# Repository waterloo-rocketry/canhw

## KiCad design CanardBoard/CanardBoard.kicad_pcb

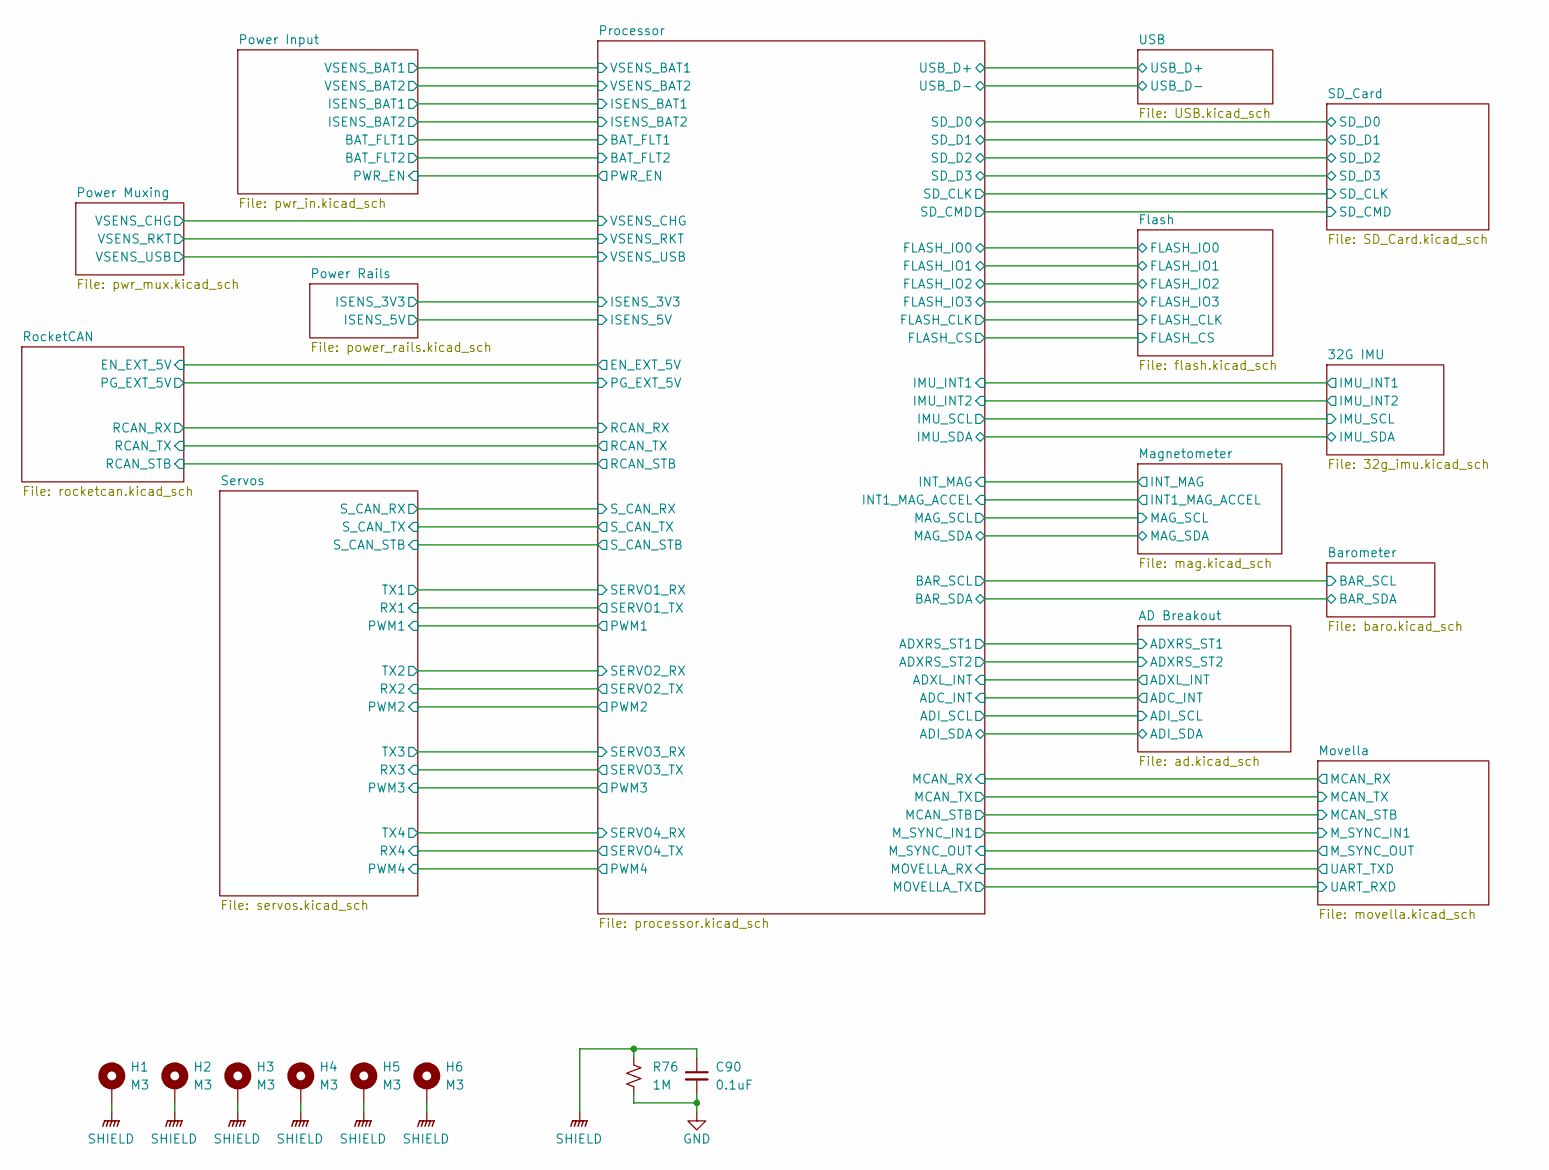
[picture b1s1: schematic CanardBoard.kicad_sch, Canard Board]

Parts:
C90: 0.1uF; C_0805_2012Metric
H1, H2, H3, H4, H5, H6: M3; MountingHole_3.2mm_M3_Pad
R76: 1M; R_0805_2012Metric

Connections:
GND: C90.2, R76.2; also elsewhere on the board
SHIELD: C90.1, H1.1, H2.1, H3.1, H4.1, H5.1, H6.1, R76.1

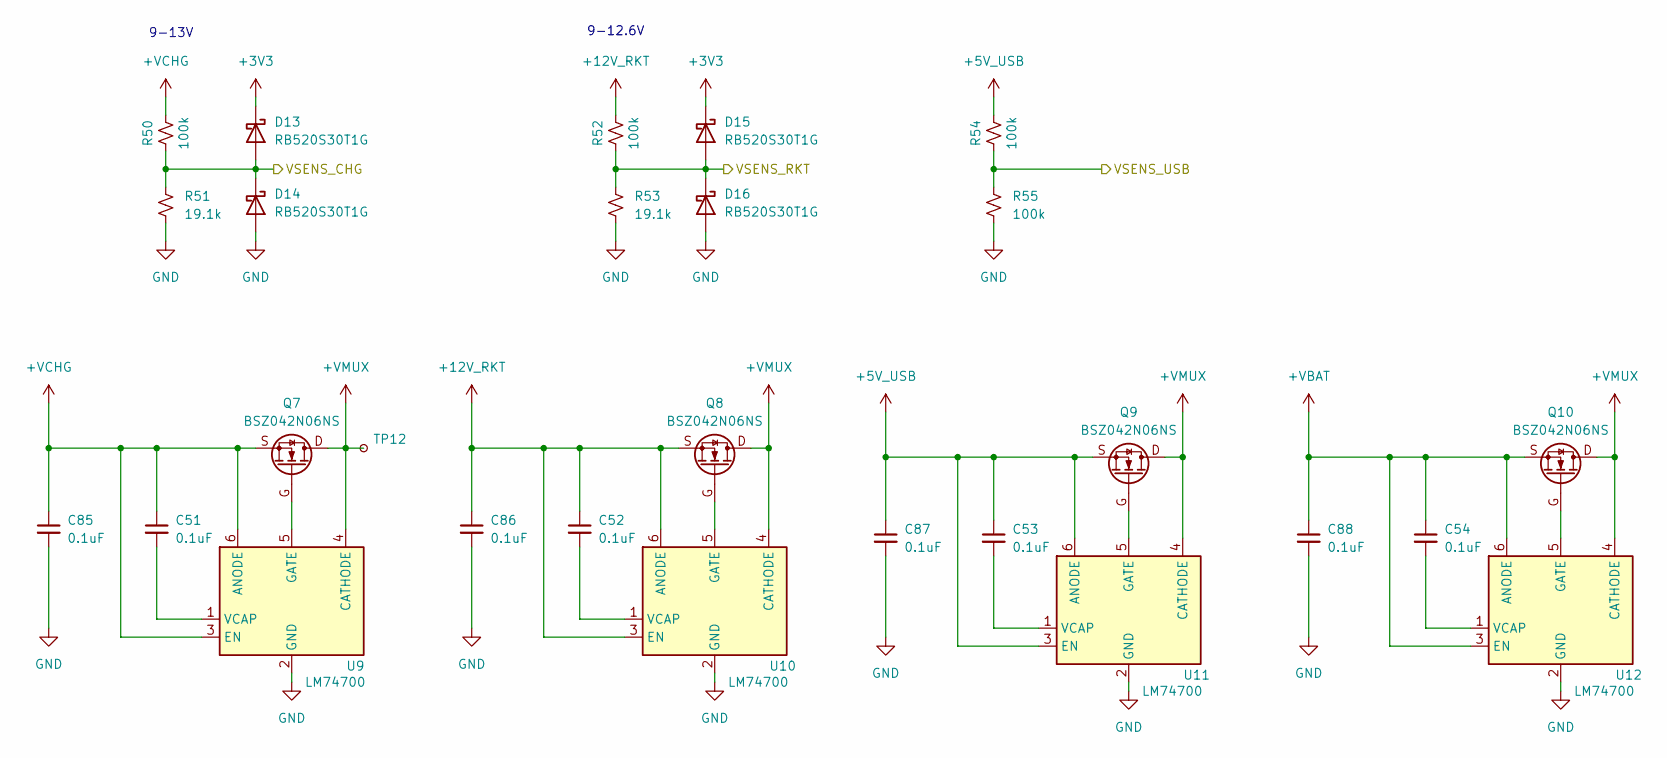
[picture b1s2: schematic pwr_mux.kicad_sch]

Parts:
C51, C52, C53, C54, C85, C86, C87, C88: 0.1uF; C_0603_1608Metric; LCSC Part # C49678
D13, D14, D15, D16: RB520S30T1G; D_SOD-523
Q7, Q8, Q9, Q10: BSZ042N06NS; Infineon-PG-TSDSON-8
R50, R52, R54: 100k; R_0402_1005Metric; LCSC Part # C17630
R51, R53: 19.1k; R_0402_1005Metric
R55: 100k; R_0402_1005Metric
TP12: VMUX; TestPoint_Pad_D1.0mm
U9, U10, U11, U12: LM74700; SOT-23-6

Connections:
+3V3: D13.1 (K), D15.1 (K); also elsewhere on the board
+5V_USB: C53.1, C87.1, Q9.S, R54.1, U11.3 (EN), U11.6 (ANODE); also elsewhere on the board
+12V_RKT: C52.1, C86.1, Q8.S, R52.1, U10.3 (EN), U10.6 (ANODE); also elsewhere on the board
+VBAT: C54.1, C88.1, Q10.S, U12.3 (EN), U12.6 (ANODE); also elsewhere on the board
+VCHG: C51.1, C85.1, Q7.S, R50.1, U9.3 (EN), U9.6 (ANODE); also elsewhere on the board
+VMUX: Q7.D, Q8.D, Q9.D, Q10.D, TP12.1, U9.4 (CATHODE), U10.4 (CATHODE), U11.4 (CATHODE), U12.4 (CATHODE); also elsewhere on the board
/Power Muxing/VSENS_CHG: D13.2 (A), D14.1 (K), R50.2, R51.2; also elsewhere on the board
/Power Muxing/VSENS_RKT: D15.2 (A), D16.1 (K), R52.2, R53.2; also elsewhere on the board
/Power Muxing/VSENS_USB: R54.2, R55.2; also elsewhere on the board
GND: C85.2, C86.2, C87.2, C88.2, D14.2 (A), D16.2 (A), R51.1, R53.1, R55.1, U9.2 (GND), U10.2 (GND), U11.2 (GND), U12.2 (GND); also elsewhere on the board
unnamed: Q7.G, U9.5 (GATE)
unnamed: C51.2, U9.1 (VCAP)
unnamed: Q8.G, U10.5 (GATE)
unnamed: C52.2, U10.1 (VCAP)
unnamed: Q9.G, U11.5 (GATE)
unnamed: C53.2, U11.1 (VCAP)
unnamed: Q10.G, U12.5 (GATE)
unnamed: C54.2, U12.1 (VCAP)

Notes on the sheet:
9-13V
9-12.6V

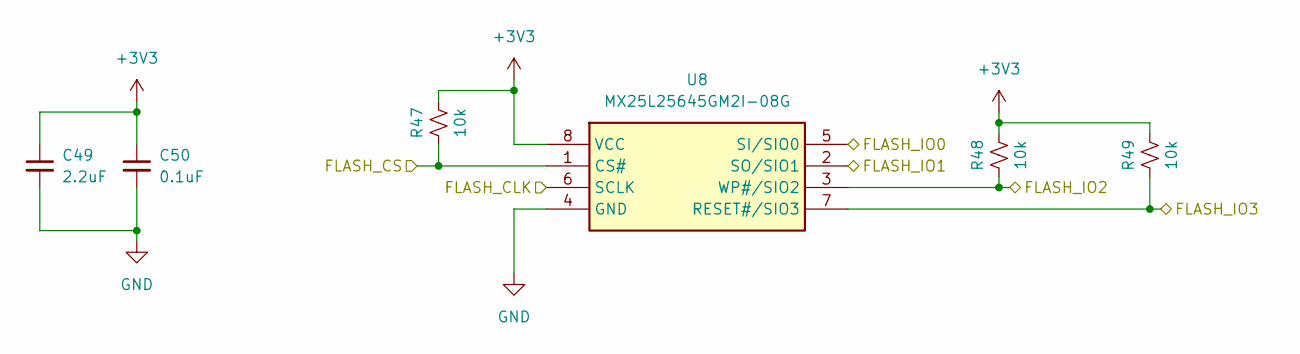
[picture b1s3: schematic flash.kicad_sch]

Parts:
C49: 2.2uF; C_0402_1005Metric; LCSC Part # C49678
C50: 0.1uF; C_0402_1005Metric; LCSC Part # C49678
R47, R48, R49: 10k; R_0402_1005Metric; LCSC Part # C17414
U8: MX25L25645GM2I-08G; Mouser Part Number 95-25L25645GM2I0TR

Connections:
+3V3: C49.1, C50.1, R47.1, R48.1, R49.1, U8.8 (VCC); also elsewhere on the board
/Flash/FLASH_CLK: U8.6 (SCLK); also elsewhere on the board
/Flash/FLASH_CS: R47.2, U8.1 (CS#); also elsewhere on the board
/Flash/FLASH_IO0: U8.5 (SI/SIO0); also elsewhere on the board
/Flash/FLASH_IO1: U8.2 (SO/SIO1); also elsewhere on the board
/Flash/FLASH_IO2: R48.2, U8.3 (WP#/SIO2); also elsewhere on the board
/Flash/FLASH_IO3: R49.2, U8.7 (RESET#/SIO3); also elsewhere on the board
GND: C49.2, C50.2, U8.4 (GND); also elsewhere on the board

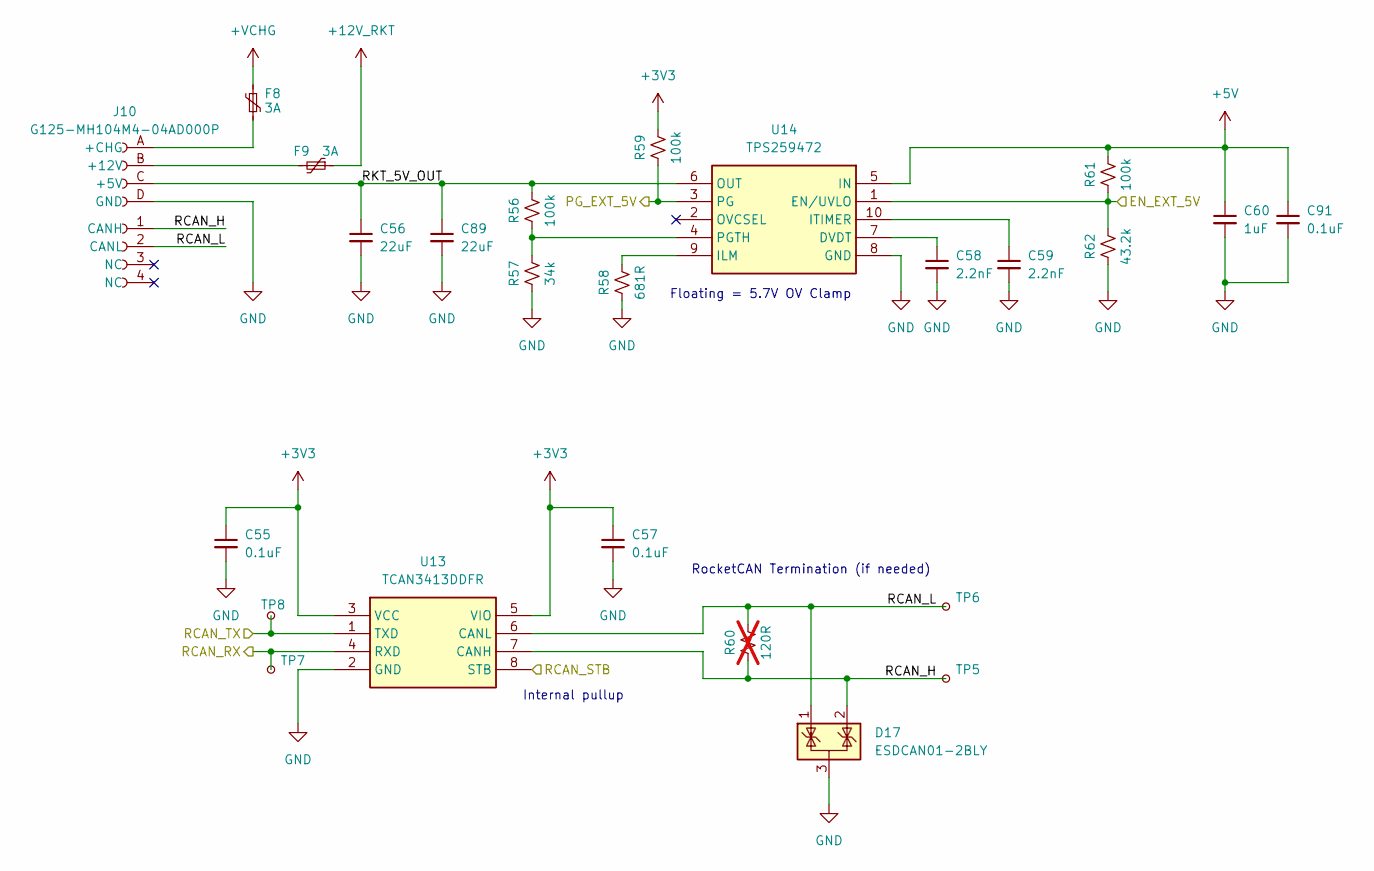
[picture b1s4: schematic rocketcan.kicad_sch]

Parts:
C55, C57, C91: 0.1uF; C_0402_1005Metric; LCSC Part # C49678
C56, C89: 22uF; C_0805_2012Metric; LCSC Part # C49678
C58, C59: 2.2nF; C_0402_1005Metric; LCSC Part # C49678
C60: 1uF; C_0402_1005Metric; LCSC Part # C49678
D17: ESDCAN01-2BLY; SOT-23
F8, F9: 3A; Fuse_0805_2012Metric
J10: G125-MH104M4-04AD000P; connector_Harwin_G125-MH104M4-04AD000P
R56, R59, R61: 100k; R_0402_1005Metric; LCSC Part # C17630
R57: 34k; R_0402_1005Metric; LCSC Part # C17630
R58: 681R; R_0402_1005Metric; LCSC Part # C17630
R60: 120R; R_0805_2012Metric; LCSC Part # C17630; not fitted
R62: 43.2k; R_0402_1005Metric; LCSC Part # C17630
TP5: RCAN_H; TestPoint_Pad_D1.0mm
TP6: RCAN_L; TestPoint_Pad_D1.0mm
TP7: RCAN_RX; TestPoint_Pad_D1.0mm
TP8: RCAN_TX; TestPoint_Pad_D1.0mm
U13: TCAN3413DDFR; Mouser Part Number 595-TCAN3413DDFR
U14: TPS259472; TPS25947xx; Mouser Part Number 595-TPS25210LRPWR

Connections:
+3V3: C55.1, C57.1, R59.1, U13.3 (VCC), U13.5 (VIO); also elsewhere on the board
+5V: C60.1, C91.1, R61.1, U14.5 (IN); also elsewhere on the board
+12V_RKT: F9.1; also elsewhere on the board
+VCHG: F8.1; also elsewhere on the board
/Processor/EN_EXT_5V: R61.2, R62.1, U14.1 (EN/UVLO); also elsewhere on the board
/Processor/PG_EXT_5V: R59.2, U14.3 (PG); also elsewhere on the board
/Processor/RCAN_RX: TP7.1, U13.4 (RXD); also elsewhere on the board
/Processor/RCAN_STB: U13.8 (STB); also elsewhere on the board
/Processor/RCAN_TX: TP8.1, U13.1 (TXD); also elsewhere on the board
/RocketCAN/RCAN_H: D17.2 (K), J10.1 (CANH), R60.2, TP5.1, U13.7 (CANH)
/RocketCAN/RCAN_L: D17.1 (K), J10.2 (CANL), R60.1, TP6.1, U13.6 (CANL)
/RocketCAN/RKT_5V_OUT: C56.1, C89.1, J10.C (+5V), R56.1, U14.6 (OUT)
GND: C55.2, C56.2, C57.2, C58.2, C59.2, C60.2, C89.2, C91.2, D17.3 (A), J10.D (GND), R57.2, R58.2, R62.2, U13.2 (GND), U14.8 (GND); also elsewhere on the board
unnamed: F9.2, J10.B (+12V)
unnamed: F8.2, J10.A (+CHG)
unnamed: C58.1, U14.7 (DVDT)
unnamed: R58.1, U14.9 (ILM)
unnamed: C59.1, U14.10 (ITIMER)
unnamed: R56.2, R57.1, U14.4 (PGTH)

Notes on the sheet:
Floating = 5.7V OV Clamp
RocketCAN Termination (if needed)
Internal pullup

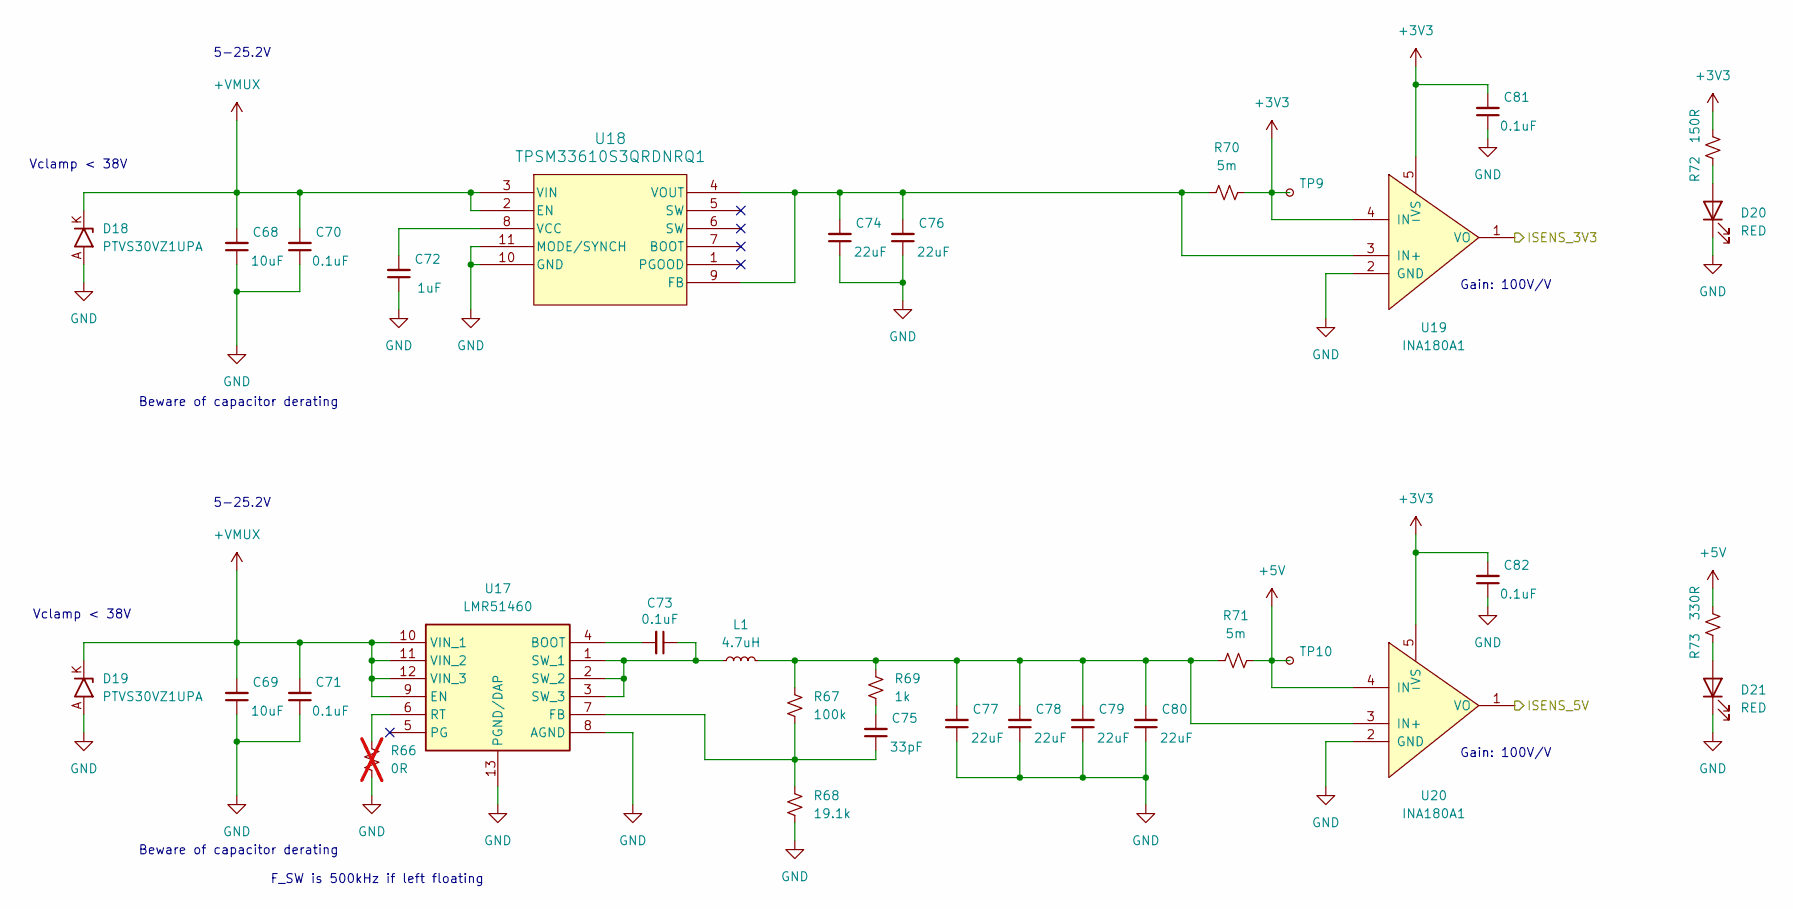
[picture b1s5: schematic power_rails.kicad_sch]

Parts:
C68, C69: 10uF; C_1210_3225Metric; LCSC Part # C49678
C70, C71: 0.1uF; C_0603_1608Metric; LCSC Part # C49678
C72: 1uF; C_0402_1005Metric; LCSC Part # C49678
C73, C81, C82: 0.1uF; C_0402_1005Metric; LCSC Part # C49678
C74, C76, C77, C78, C79, C80: 22uF; C_0805_2012Metric; LCSC Part # C49678
C75: 33pF; C_0402_1005Metric; LCSC Part # C49678
D18, D19: PTVS30VZ1UPA; PTVS30VZ1UPAZ
D20, D21: RED; LED_0603_1608Metric
L1: 4.7uH; SRP7050WA; MPN SRP7050WA-4R7M
R66: 0R; R_0402_1005Metric; not fitted
R67: 100k; R_0402_1005Metric
R68: 19.1k; R_0402_1005Metric
R69: 1k; R_0402_1005Metric
R70, R71: 5m; R_0805_2012Metric
R72: 150R; R_0402_1005Metric; LCSC Part # C17471
R73: 330R; R_0402_1005Metric; LCSC Part # C17471
TP9: 3V3; TestPoint_Pad_D1.0mm
TP10: 5V; TestPoint_Pad_D1.0mm
U17: LMR51460
U18: TPSM33610S3QRDNRQ1; TPSM33606S3QRDNRQ1
U19, U20: INA180A1; SOT-23-5

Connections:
+3V3: C81.2, C82.2, R70.1, R72.1, TP9.1, U19.4 (IN-), U19.5 (VS), U20.5 (VS); also elsewhere on the board
+5V: R71.1, R73.1, TP10.1, U20.4 (IN-); also elsewhere on the board
+VMUX: C68.2, C69.2, C70.2, C71.2, D18.K, D19.K, U17.9 (EN), U17.10 (VIN_1), U17.11 (VIN_2), U17.12 (VIN_3), U18.2 (EN), U18.3 (VIN); also elsewhere on the board
/Power Rails/ISENS_3V3: U19.1 (VO); also elsewhere on the board
/Power Rails/ISENS_5V: U20.1 (VO); also elsewhere on the board
GND: C68.1, C69.1, C70.1, C71.1, C72.1, C74.1, C76.1, C77.1, C78.1, C79.1, C80.1, C81.1, C82.1, D18.A, D19.A, D20.1 (K), D21.1 (K), R66.1, R68.1, U17.8 (AGND), U17.13 (PGND/DAP), U18.10 (GND), U18.11 (MODE/SYNCH), U19.2 (GND), U20.2 (GND); also elsewhere on the board
unnamed: C75.2, R69.1
unnamed: D20.2 (A), R72.2
unnamed: D21.2 (A), R73.2
unnamed: C73.2, U17.4 (BOOT)
unnamed: C75.1, R67.1, R68.2, U17.7 (FB)
unnamed: R66.2, U17.6 (RT)
unnamed: C73.1, L1.1, U17.1 (SW_1), U17.2 (SW_2), U17.3 (SW_3)
unnamed: C74.2, C76.2, R70.2, U18.4 (VOUT), U18.9 (FB), U19.3 (IN+)
unnamed: C72.2, U18.8 (VCC)
unnamed: C77.2, C78.2, C79.2, C80.2, L1.2, R67.2, R69.2, R71.2, U20.3 (IN+)

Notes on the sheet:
5-25.2V
Beware of capacitor derating
F_SW is 500kHz if left floating
Gain: 100V/V
Vclamp < 38V

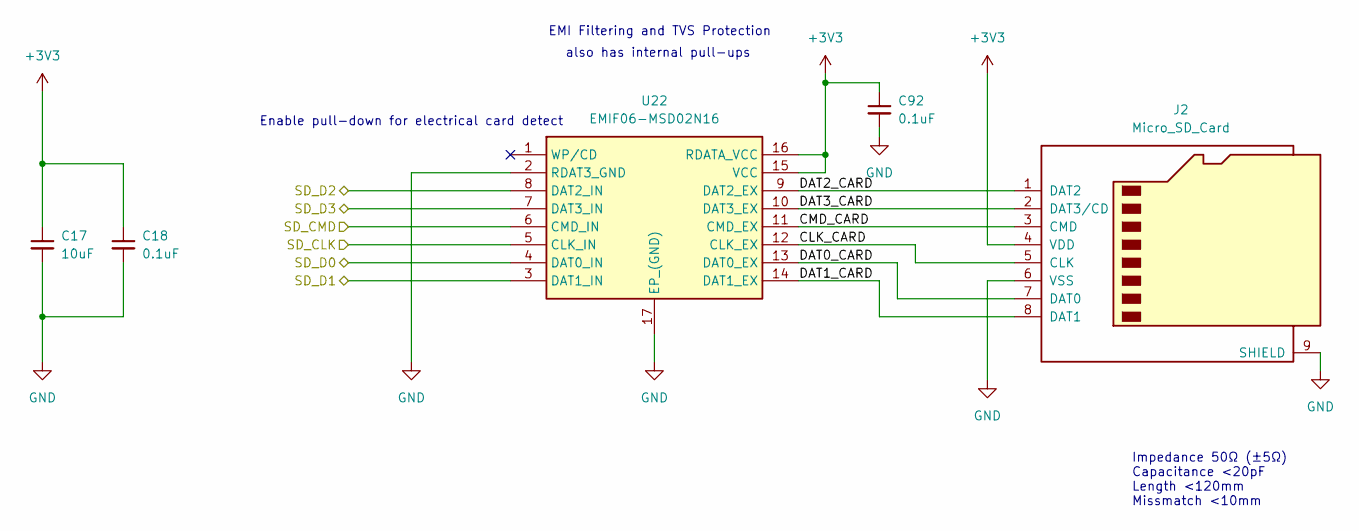
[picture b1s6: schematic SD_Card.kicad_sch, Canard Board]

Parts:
C17: 10uF; C_0603_1608Metric; LCSC Part # C49678
C18, C92: 0.1uF; C_0402_1005Metric; LCSC Part # C49678
J2: Micro_SD_Card; microSD_HC_Molex_47219-2001
U22: EMIF06-MSD02N16; EMIF06MSD02N16

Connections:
+3V3: C17.1, C18.1, C92.1, J2.4 (VDD), U22.15 (VCC), U22.16 (RDATA_VCC); also elsewhere on the board
/Processor/SD_CLK: U22.5 (CLK_IN); also elsewhere on the board
/Processor/SD_CMD: U22.6 (CMD_IN); also elsewhere on the board
/Processor/SD_D0: U22.4 (DAT0_IN); also elsewhere on the board
/Processor/SD_D1: U22.3 (DAT1_IN); also elsewhere on the board
/Processor/SD_D2: U22.8 (DAT2_IN); also elsewhere on the board
/Processor/SD_D3: U22.7 (DAT3_IN); also elsewhere on the board
/SD_Card/CLK_CARD: J2.5 (CLK), U22.12 (CLK_EX)
/SD_Card/CMD_CARD: J2.3 (CMD), U22.11 (CMD_EX)
/SD_Card/DAT0_CARD: J2.7 (DAT0), U22.13 (DAT0_EX)
/SD_Card/DAT1_CARD: J2.8 (DAT1), U22.14 (DAT1_EX)
/SD_Card/DAT2_CARD: J2.1 (DAT2), U22.9 (DAT2_EX)
/SD_Card/DAT3_CARD: J2.2 (DAT3/CD), U22.10 (DAT3_EX)
GND: C17.2, C18.2, C92.2, J2.6 (VSS), J2.9 (SHIELD), U22.2 (RDAT3_GND), U22.17 (EP_(GND)); also elsewhere on the board

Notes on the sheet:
also has internal pull-ups
Impedance 50Ω (±5Ω) Capacitance <20pF Length <120mm Missmatch <10mm
EMI Filtering and TVS Protection
Enable pull-down for electrical card detect

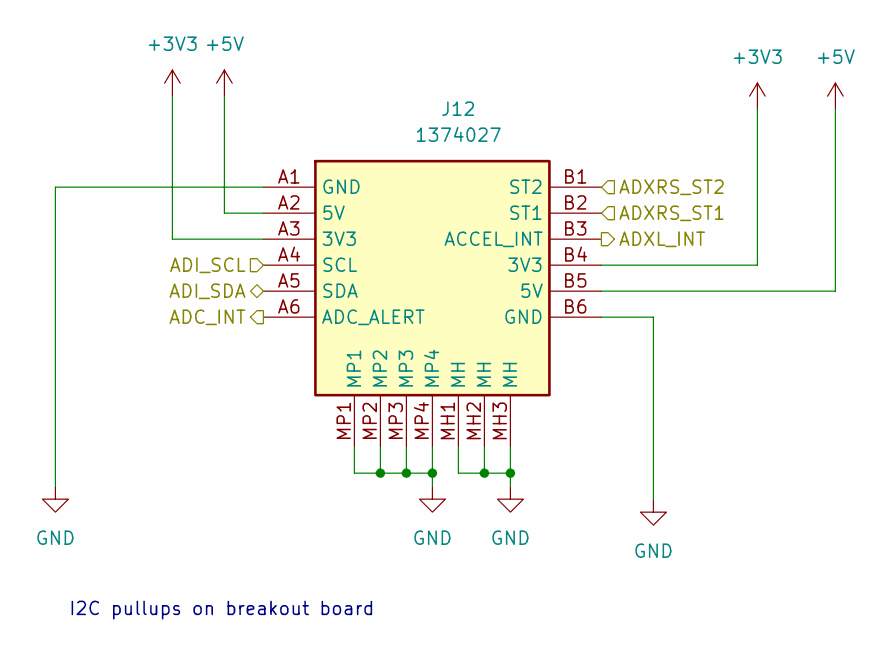
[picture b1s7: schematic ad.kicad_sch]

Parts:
J12: 1374027; Mouser Part Number 651-1374027

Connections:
+3V3: J12.A3 (3V3), J12.B4 (3V3); also elsewhere on the board
+5V: J12.A2 (5V), J12.B5 (5V); also elsewhere on the board
/AD Breakout/ADC_INT: J12.A6 (ADC_ALERT); also elsewhere on the board
/AD Breakout/ADI_SCL: J12.A4 (SCL); also elsewhere on the board
/AD Breakout/ADI_SDA: J12.A5 (SDA); also elsewhere on the board
/AD Breakout/ADXL_INT: J12.B3 (ACCEL_INT); also elsewhere on the board
/AD Breakout/ADXRS_ST1: J12.B2 (ST1); also elsewhere on the board
/AD Breakout/ADXRS_ST2: J12.B1 (ST2); also elsewhere on the board
GND: J12.A1 (GND), J12.B6 (GND), J12.MH1 (MH), J12.MH2 (MH), J12.MH3 (MH), J12.MP1, J12.MP2, J12.MP3, J12.MP4; also elsewhere on the board

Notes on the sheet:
I2C pullups on breakout board

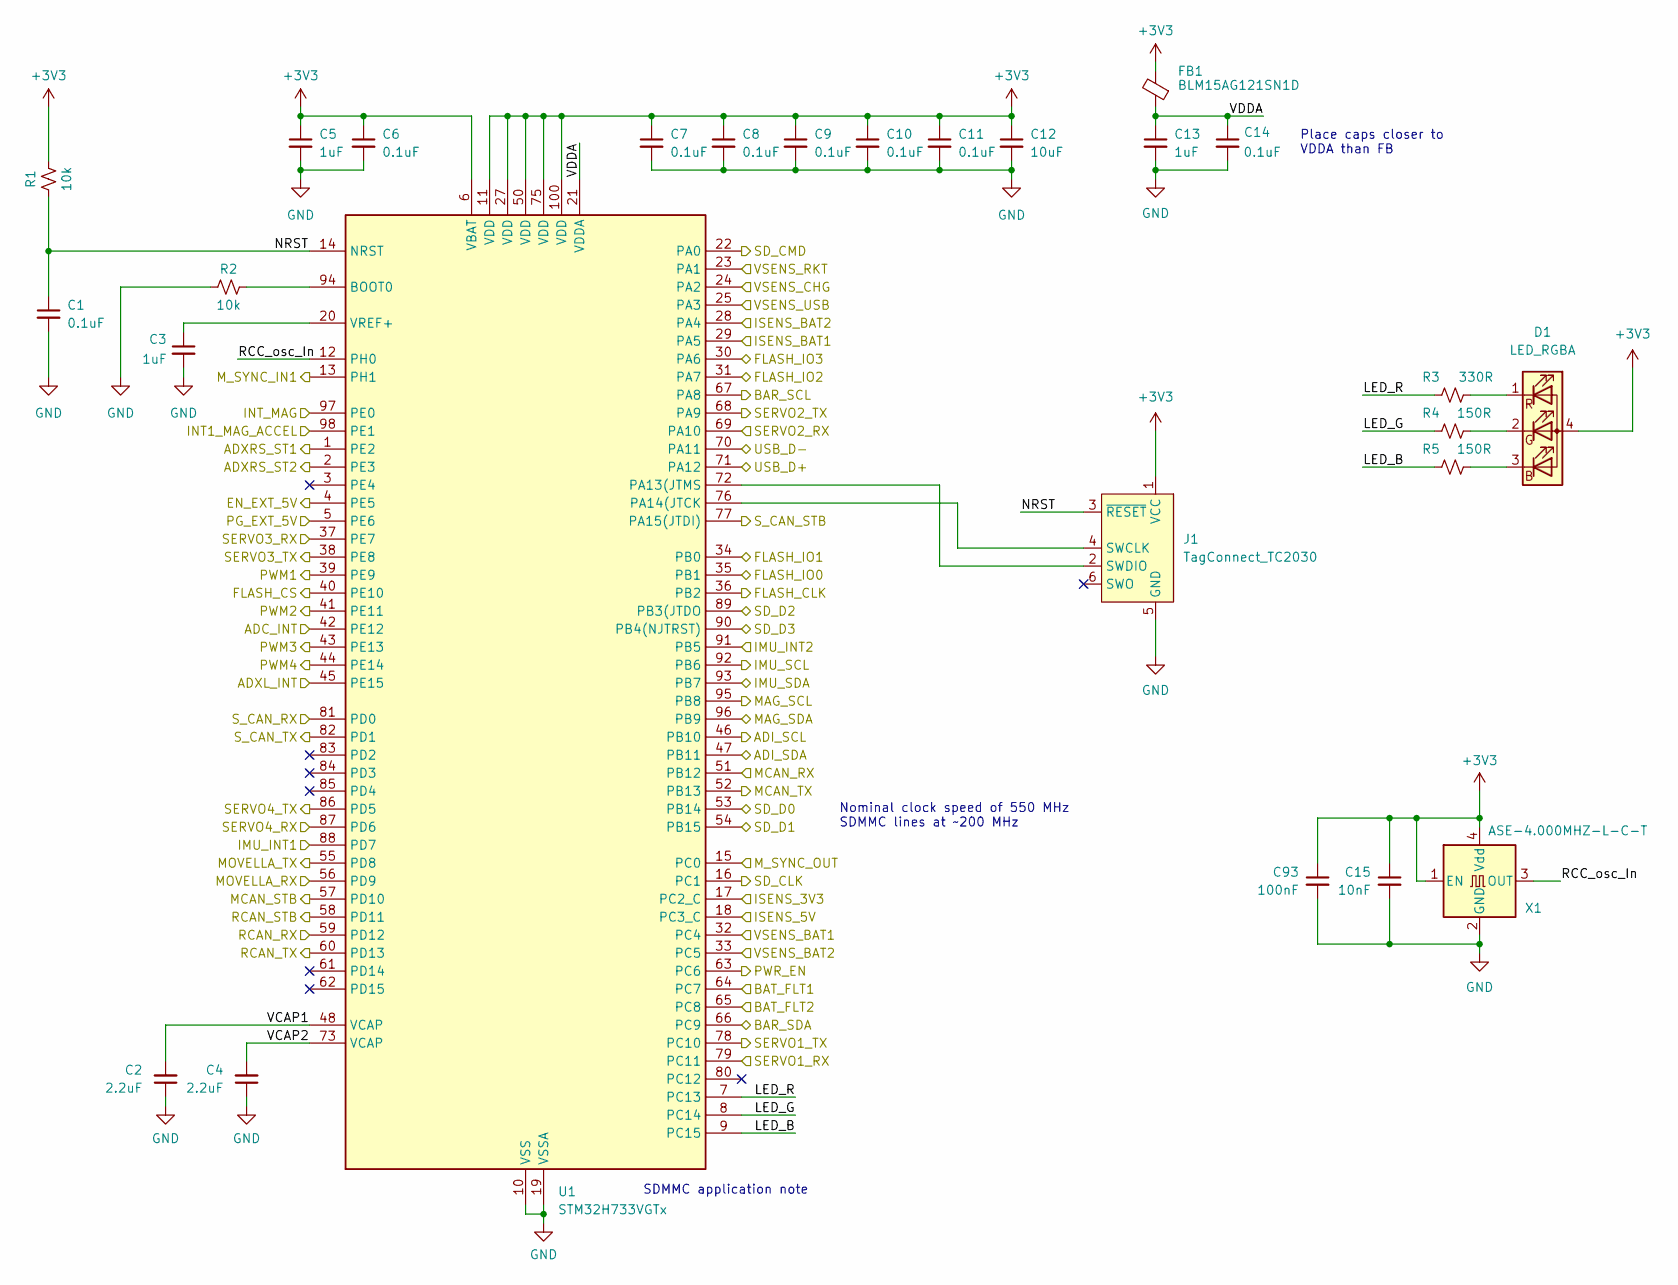
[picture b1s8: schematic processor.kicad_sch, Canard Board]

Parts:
C1, C6, C7, C8, C9, C10, C11, C14: 0.1uF; C_0402_1005Metric; LCSC Part # C49678
C2, C4: 2.2uF; C_0402_1005Metric; LCSC Part # C377773
C3, C5, C13: 1uF; C_0402_1005Metric; LCSC Part # C28323
C12: 10uF; C_0603_1608Metric; LCSC Part # C49678
C15: 10nF; C_0402_1005Metric; LCSC Part # C1710
C93: 100nF; C_0402_1005Metric; LCSC Part # C1710
D1: LED_RGBA; EAST1616RGBB2
FB1: BLM15AG121SN1D; C_0402_1005Metric
J1: TagConnect_TC2030; Tag-Connect_TC2030-IDC-FP_2x03_P1.27mm_Vertical
R1, R2: 10k; R_0402_1005Metric; LCSC Part # C17414
R3: 330R; R_0402_1005Metric; LCSC Part # C17630
R4, R5: 150R; R_0402_1005Metric; LCSC Part # C17471
U1: STM32H733VGTx; LQFP-100_14x14mm_P0.5mm; LCSC Part # C730160
X1: ASE-4.000MHZ-L-C-T; Oscillator_SMD_Abracon_ASE-4Pin_3.2x2.5mm; LCSC Part # C437121

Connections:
+3V3: C5.1, C6.1, C7.1, C8.1, C9.1, C10.1, C11.1, C12.1, C15.1, C93.1, D1.4 (A), FB1.2, J1.1 (VCC), R1.1, U1.6 (VBAT), U1.11 (VDD), U1.27 (VDD), U1.50 (VDD), U1.75 (VDD), U1.100 (VDD), X1.1 (EN), X1.4 (Vdd); also elsewhere on the board
/32G IMU/IMU_INT1: U1.88 (PD7); also elsewhere on the board
/32G IMU/IMU_INT2: U1.91 (PB5); also elsewhere on the board
/32G IMU/IMU_SCL: U1.92 (PB6); also elsewhere on the board
/32G IMU/IMU_SDA: U1.93 (PB7); also elsewhere on the board
/AD Breakout/ADC_INT: U1.42 (PE12); also elsewhere on the board
/AD Breakout/ADI_SCL: U1.46 (PB10); also elsewhere on the board
/AD Breakout/ADI_SDA: U1.47 (PB11); also elsewhere on the board
/AD Breakout/ADXL_INT: U1.45 (PE15); also elsewhere on the board
/AD Breakout/ADXRS_ST1: U1.1 (PE2); also elsewhere on the board
/AD Breakout/ADXRS_ST2: U1.2 (PE3); also elsewhere on the board
/Barometer/BAR_SCL: U1.67 (PA8); also elsewhere on the board
/Barometer/BAR_SDA: U1.66 (PC9); also elsewhere on the board
/Flash/FLASH_CLK: U1.36 (PB2); also elsewhere on the board
/Flash/FLASH_CS: U1.40 (PE10); also elsewhere on the board
/Flash/FLASH_IO0: U1.35 (PB1); also elsewhere on the board
/Flash/FLASH_IO1: U1.34 (PB0); also elsewhere on the board
/Flash/FLASH_IO2: U1.31 (PA7); also elsewhere on the board
/Flash/FLASH_IO3: U1.30 (PA6); also elsewhere on the board
/Magnetometer/INT1_MAG_ACCEL: U1.98 (PE1); also elsewhere on the board
/Magnetometer/INT_MAG: U1.97 (PE0); also elsewhere on the board
/Magnetometer/MAG_SCL: U1.95 (PB8); also elsewhere on the board
/Magnetometer/MAG_SDA: U1.96 (PB9); also elsewhere on the board
/Movella/MCAN_RX: U1.51 (PB12); also elsewhere on the board
/Movella/MCAN_STB: U1.57 (PD10); also elsewhere on the board
/Movella/MCAN_TX: U1.52 (PB13); also elsewhere on the board
/Movella/M_SYNC_IN1: U1.13 (PH1); also elsewhere on the board
/Movella/M_SYNC_OUT: U1.15 (PC0); also elsewhere on the board
/Movella/UART_RXD: U1.55 (PD8); also elsewhere on the board
/Movella/UART_TXD: U1.56 (PD9); also elsewhere on the board
/Power Input/BAT_FLT1: U1.64 (PC7); also elsewhere on the board
/Power Input/BAT_FLT2: U1.65 (PC8); also elsewhere on the board
/Power Input/ISENS_BAT1: U1.29 (PA5); also elsewhere on the board
/Power Input/ISENS_BAT2: U1.28 (PA4); also elsewhere on the board
/Power Input/PWR_EN: U1.63 (PC6); also elsewhere on the board
/Power Input/VSENS_BAT1: U1.32 (PC4); also elsewhere on the board
/Power Input/VSENS_BAT2: U1.33 (PC5); also elsewhere on the board
/Power Muxing/VSENS_CHG: U1.24 (PA2); also elsewhere on the board
/Power Muxing/VSENS_RKT: U1.23 (PA1); also elsewhere on the board
/Power Muxing/VSENS_USB: U1.25 (PA3); also elsewhere on the board
/Power Rails/ISENS_3V3: U1.17 (PC2_C); also elsewhere on the board
/Power Rails/ISENS_5V: U1.18 (PC3_C); also elsewhere on the board
/Processor/EN_EXT_5V: U1.4 (PE5); also elsewhere on the board
/Processor/LED_B: R5.2, U1.9 (PC15)
/Processor/LED_G: R4.2, U1.8 (PC14)
/Processor/LED_R: R3.2, U1.7 (PC13)
/Processor/NRST: C1.1, J1.3 (~RESET), R1.2, U1.14 (NRST)
/Processor/PG_EXT_5V: U1.5 (PE6); also elsewhere on the board
/Processor/PWM1: U1.39 (PE9); also elsewhere on the board
/Processor/PWM2: U1.41 (PE11); also elsewhere on the board
/Processor/PWM3: U1.43 (PE13); also elsewhere on the board
/Processor/PWM4: U1.44 (PE14); also elsewhere on the board
/Processor/RCAN_RX: U1.59 (PD12); also elsewhere on the board
/Processor/RCAN_STB: U1.58 (PD11); also elsewhere on the board
/Processor/RCAN_TX: U1.60 (PD13); also elsewhere on the board
/Processor/RCC_osc_In: U1.12 (PH0), X1.3 (OUT)
/Processor/SD_CLK: U1.16 (PC1); also elsewhere on the board
/Processor/SD_CMD: U1.22 (PA0); also elsewhere on the board
/Processor/SD_D0: U1.53 (PB14); also elsewhere on the board
/Processor/SD_D1: U1.54 (PB15); also elsewhere on the board
/Processor/SD_D2: U1.89 (PB3(JTDO); also elsewhere on the board
/Processor/SD_D3: U1.90 (PB4(NJTRST)); also elsewhere on the board
/Processor/SERVO1_RX: U1.79 (PC11); also elsewhere on the board
/Processor/SERVO1_TX: U1.78 (PC10); also elsewhere on the board
/Processor/SERVO2_RX: U1.69 (PA10); also elsewhere on the board
/Processor/SERVO2_TX: U1.68 (PA9); also elsewhere on the board
/Processor/SERVO3_RX: U1.37 (PE7); also elsewhere on the board
/Processor/SERVO3_TX: U1.38 (PE8); also elsewhere on the board
/Processor/SERVO4_RX: U1.87 (PD6); also elsewhere on the board
/Processor/SERVO4_TX: U1.86 (PD5); also elsewhere on the board
/Processor/S_CAN_RX: U1.81 (PD0); also elsewhere on the board
/Processor/S_CAN_STB: U1.77 (PA15(JTDI)); also elsewhere on the board
/Processor/S_CAN_TX: U1.82 (PD1); also elsewhere on the board
/Processor/USB_D+: U1.71 (PA12); also elsewhere on the board
/Processor/USB_D-: U1.70 (PA11); also elsewhere on the board
/Processor/VCAP1: C2.2, U1.48 (VCAP)
/Processor/VCAP2: C4.2, U1.73 (VCAP)
/Processor/VDDA: C13.1, C14.1, FB1.1, U1.21 (VDDA)
GND: C1.2, C2.1, C3.2, C4.1, C5.2, C6.2, C7.2, C8.2, C9.2, C10.2, C11.2, C12.2, C13.2, C14.2, C15.2, C93.2, J1.5 (GND), R2.2, U1.10 (VSS), U1.19 (VSSA), U1.26 (VSS), U1.49 (VSS), U1.74 (VSS), U1.99 (VSS), X1.2 (GND); also elsewhere on the board
unnamed: D1.3 (BK), R5.1
unnamed: D1.2 (GK), R4.1
unnamed: D1.1 (RK), R3.1
unnamed: J1.4 (SWCLK), U1.76 (PA14(JTCK)
unnamed: J1.2 (SWDIO), U1.72 (PA13(JTMS)
unnamed: R2.1, U1.94 (BOOT0)
unnamed: C3.1, U1.20 (VREF+)

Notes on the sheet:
SDMMC application note
Place caps closer to VDDA than FB
Nominal clock speed of 550 MHz SDMMC lines at ~200 MHz

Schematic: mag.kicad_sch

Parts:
C61, C62: 0.1uF; C_0402_1005Metric; LCSC Part # C49678
C63: 4.7uF; C_0402_1005Metric; LCSC Part # C49678
C64: 220nF; C_0402_1005Metric; LCSC Part # C49678
R63, R64: 1k; R_0402_1005Metric
U15: LSM303AGR; LGA-12_2x2mm_P0.5mm

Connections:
+3V3: C61.2, C62.2, C63.2, R63.2, R64.2, U15.2 (CS_XL), U15.3 (CS_MAG), U15.9 (VDD), U15.10 (VDDIO); also elsewhere on the board
/Magnetometer/INT1_MAG_ACCEL: U15.12 (INT_1_XL); also elsewhere on the board
/Magnetometer/INT_MAG: U15.7 (INT_MAG/DRDY); also elsewhere on the board
/Magnetometer/MAG_SCL: R64.1, U15.1 (SCL/SPC); also elsewhere on the board
/Magnetometer/MAG_SDA: R63.1, U15.4 (SDA/SDI/SDO); also elsewhere on the board
GND: C61.1, C62.1, C63.1, C64.1, U15.6 (GND), U15.8 (GND); also elsewhere on the board
unnamed: C64.2, U15.5 (C1)

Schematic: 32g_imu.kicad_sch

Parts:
C83, C84: 0.1uF; C_0402_1005Metric; LCSC Part # C49678
R74, R75: 1k; R_0402_1005Metric; LCSC Part # C17630
U21: LSM6DSV32XTR

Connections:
+3V3: C83.1, C84.1, R74.1, R75.1, U21.5 (VDD_IO), U21.8 (VDD), U21.12 (CS); also elsewhere on the board
/32G IMU/IMU_INT1: U21.4 (INT1); also elsewhere on the board
/32G IMU/IMU_INT2: U21.9 (INT2); also elsewhere on the board
/32G IMU/IMU_SCL: R75.2, U21.13 (SCL); also elsewhere on the board
/32G IMU/IMU_SDA: R74.2, U21.14 (SDA); also elsewhere on the board
GND: C83.2, C84.2, U21.1 (SDO/SA0), U21.2 (SDX/AH1/QVAR1), U21.3 (SCX/AH2/QVAR2), U21.6 (GND), U21.7 (GND); also elsewhere on the board

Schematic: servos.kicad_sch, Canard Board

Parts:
C37, C40: 0.1uF; C_0402_1005Metric; LCSC Part # C49678
C38, C41, C43, C45: 10uF; C_1210_3225Metric; LCSC Part # C49678
C39, C42, C44, C46: 220uF; A786MW227M1HLAV011; MPN A786MW227M1HLAV011
D8, D9, D11, D12: SMAJ28CA; D_SMA
D10: ESDCAN01-2BLY; SOT-23
F3, F4, F5, F6: 10A; Fuse_1206_3216Metric
J5: Motor 2; G125MH10805M41AD1ADP; Mouser Part Number 855-GMH1085M41AD1ADP
J6: Motor 1; G125MH10805M41AD1ADP; Mouser Part Number 855-GMH1085M41AD1ADP
J7: Motor 4; G125MH10805M41AD1ADP; Mouser Part Number 855-GMH1085M41AD1ADP
J8: Motor 3; G125MH10805M41AD1ADP; Mouser Part Number 855-GMH1085M41AD1ADP
JP1, JP2, JP3, JP4, JP5, JP6, JP7, JP8: SolderJumper_2_Open; SolderJumper-2_P1.3mm_Open_RoundedPad1.0x1.5mm
R43, R44: 120R; R_0805_2012Metric; LCSC Part # C17630
TP1: S_CAN_H; TestPoint_Pad_D1.0mm
TP2: S_CAN_L; TestPoint_Pad_D1.0mm
TP3: S_CAN_RX; TestPoint_Pad_D1.0mm
TP4: S_CAN_TX; TestPoint_Pad_D1.0mm
U6: TCAN3413DDFR; Mouser Part Number 595-TCAN3413DDFR

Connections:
+3V3: C37.1, C40.1, U6.3 (VCC), U6.5 (VIO); also elsewhere on the board
+VBAT: C38.1, C39.1, C41.1, C42.1, C43.1, C44.1, C45.1, C46.1, D8.1 (A1), D9.1 (A1), D11.1 (A1), D12.1 (A1), F3.2, F4.2, F5.2, F6.2; also elsewhere on the board
/Processor/PWM1: J6.5; also elsewhere on the board
/Processor/PWM2: J5.5; also elsewhere on the board
/Processor/PWM3: J8.5; also elsewhere on the board
/Processor/PWM4: J7.5; also elsewhere on the board
/Processor/SERVO1_RX: J6.2; also elsewhere on the board
/Processor/SERVO1_TX: J6.1; also elsewhere on the board
/Processor/SERVO2_RX: J5.2; also elsewhere on the board
/Processor/SERVO2_TX: J5.1; also elsewhere on the board
/Processor/SERVO3_RX: J8.2; also elsewhere on the board
/Processor/SERVO3_TX: J8.1; also elsewhere on the board
/Processor/SERVO4_RX: J7.2; also elsewhere on the board
/Processor/SERVO4_TX: J7.1; also elsewhere on the board
/Processor/S_CAN_RX: TP3.1, U6.4 (RXD); also elsewhere on the board
/Processor/S_CAN_STB: U6.8 (STB); also elsewhere on the board
/Processor/S_CAN_TX: TP4.1, U6.1 (TXD); also elsewhere on the board
/Servos/CANH_4: J7.7, JP3.2 (B), R44.1
/Servos/CANH_12: J5.3, J6.7, JP1.2 (B), JP7.1 (A)
/Servos/CANH_23: J5.7, J8.3, JP5.1 (A), JP7.2 (B)
/Servos/CANH_34: J7.3, J8.7, JP3.1 (A), JP5.2 (B)
/Servos/CANL_4: J7.8, JP4.2 (B), R44.2
/Servos/CANL_12: J5.4, J6.8, JP2.2 (B), JP8.1 (A)
/Servos/CANL_23: J5.8, J8.4, JP6.1 (A), JP8.2 (B)
/Servos/CANL_34: J7.4, J8.8, JP4.1 (A), JP6.2 (B)
/Servos/S_CAN_H: D10.2 (K), J6.3, JP1.1 (A), R43.2, TP1.1, U6.7 (CANH)
/Servos/S_CAN_L: D10.1 (K), J6.4, JP2.1 (A), R43.1, TP2.1, U6.6 (CANL)
GND: C37.2, C38.2, C39.2, C40.2, C41.2, C42.2, C43.2, C44.2, C45.2, C46.2, D8.2 (A2), D9.2 (A2), D10.3 (A), D11.2 (A2), D12.2 (A2), J5.6, J5.10 (A2), J5.11 (SHIELD_1), J5.12 (SHIELD_2), J6.6, J6.10 (A2), J6.11 (SHIELD_1), J6.12 (SHIELD_2), J7.6, J7.10 (A2), J7.11 (SHIELD_1), J7.12 (SHIELD_2), J8.6, J8.10 (A2), J8.11 (SHIELD_1), J8.12 (SHIELD_2), U6.2 (GND); also elsewhere on the board
unnamed: F3.1, J5.9 (A1)
unnamed: F4.1, J6.9 (A1)
unnamed: F5.1, J7.9 (A1)
unnamed: F6.1, J8.9 (A1)

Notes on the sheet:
Internal pullup
Bridge CAN lines for unused motor connectors

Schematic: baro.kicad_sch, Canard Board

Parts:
C16: 0.1uF; C_0402_1005Metric; LCSC Part # C49678
R6, R7: 2.2k; R_0402_1005Metric; LCSC Part # C17630
U2: MS5611-01BA; LGA-8_3x5mm_P1.25mm

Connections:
+3V3: C16.1, R6.1, R7.1, U2.1 (VDD), U2.2 (PS); also elsewhere on the board
/Barometer/BAR_SCL: R6.2, U2.8 (SCLK); also elsewhere on the board
/Barometer/BAR_SDA: R7.2, U2.7 (SDI/SDA); also elsewhere on the board
GND: C16.2, U2.3 (GND), U2.4 (CSB), U2.5 (CSB); also elsewhere on the board

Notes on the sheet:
CSB -> GND: I2C Addr is 1110110

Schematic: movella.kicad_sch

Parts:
C65: 22uF; C_0805_2012Metric; LCSC Part # C49678
C66, C67: 0.1uF; C_0402_1005Metric; LCSC Part # C49678
J11: Movella-1374028; Mouser Part Number 651-1374028
R65: 120R; R_0805_2012Metric; LCSC Part # C17630
U16: TCAN3413DDFR; Mouser Part Number 595-TCAN3413DDFR

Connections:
+3V3: C66.1, C67.1, U16.3 (VCC), U16.5 (VIO); also elsewhere on the board
+5V: C65.1, J11.A1 (VIN); also elsewhere on the board
/Movella/MCAN_H: J11.A2 (CAN_H), R65.2, U16.7 (CANH)
/Movella/MCAN_L: J11.B2 (CAN_L), R65.1, U16.6 (CANL)
/Movella/MCAN_RX: U16.4 (RXD); also elsewhere on the board
/Movella/MCAN_STB: U16.8 (STB); also elsewhere on the board
/Movella/MCAN_TX: U16.1 (TXD); also elsewhere on the board
/Movella/M_SYNC_IN1: J11.A5 (SYNC_IN1); also elsewhere on the board
/Movella/M_SYNC_OUT: J11.A7 (SYNC_OUT); also elsewhere on the board
/Movella/UART_RXD: J11.B8 (UART_RXD); also elsewhere on the board
/Movella/UART_TXD: J11.A8 (UART_TXD); also elsewhere on the board
GND: C65.2, C66.2, C67.2, J11.B1 (GND), J11.B7 (GND), J11.MH1 (MH), J11.MH2 (MH), J11.MH3 (MH), J11.MP1, J11.MP2, J11.MP3, J11.MP4, U16.2 (GND); also elsewhere on the board

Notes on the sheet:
Internal pullup
Movella CAN Termination
